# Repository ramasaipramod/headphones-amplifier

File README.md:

# Headphone Amplifier Using LM386

This project involves designing a headphone audio amplifier circuit using the LM386 low-voltage audio power amplifier. The amplifier boosts audio signals for use with headphones.

## Files in the Repository

- **`HeadphoneAmplifierUsingLM386.asc`**  
  LTspice simulation file to analyze the circuit's performance.
  
- **`HeadphoneAmplifierUsingLM386.brd`**  
  PCB layout file for the amplifier, which can be used to manufacture the circuit board.
  
- **`HeadphoneAmplifierUsingLM386.sch`**  
  Schematic diagram of the circuit showing all components and connections.

## Components Used
- LM386
- Resistors, capacitors, and other passive components.
- Headphone jack and connectors.

## How to Use
1. Open the **`.sch`** file in a schematic editor to view the circuit design.
2. Run the **`.asc`** file in LTspice to simulate and verify the circuit behavior.
3. Use the **`.brd`** file to fabricate the PCB, assemble the components, and test the amplifier.

## Tools Used
- **LTspice**: For circuit simulation.
- **EAGLE/Altium/Other PCB Design Software**: For schematic and PCB design.

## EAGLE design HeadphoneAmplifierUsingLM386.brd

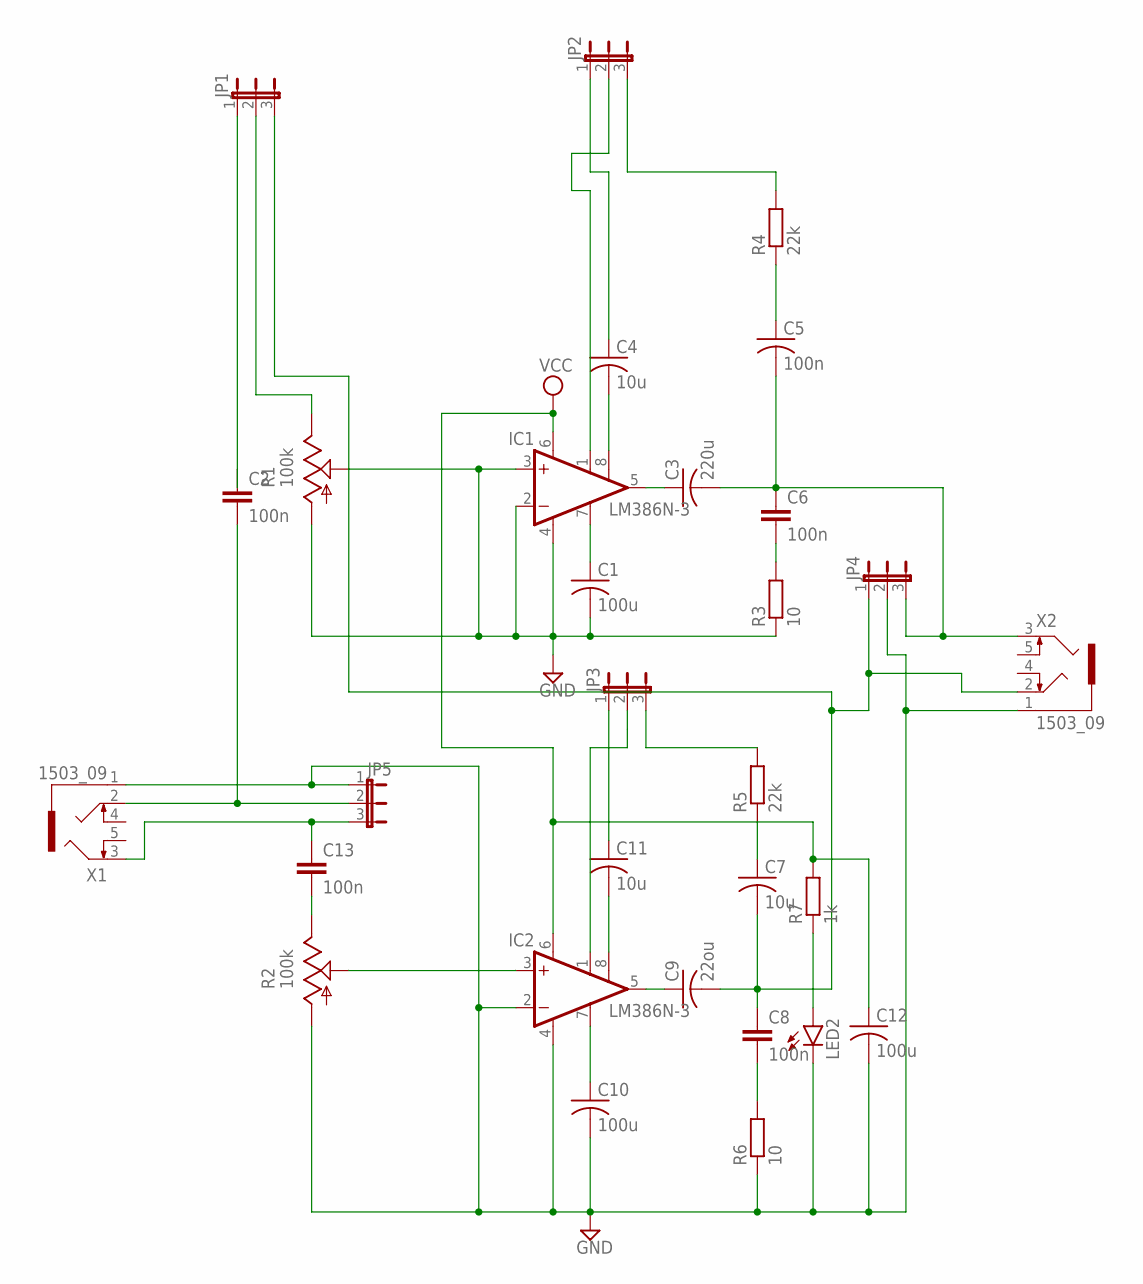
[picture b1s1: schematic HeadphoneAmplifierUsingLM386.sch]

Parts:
C1, C10, C12: 100u; C025-030X050
C2, C5, C6, C8, C13: 100n; C025-030X050
C3: 220u; C025-030X050
C4, C7, C11: 10u; C025-030X050
C9: 22ou; C025-030X050
IC1, IC2: LM386N-3; DIL08
JP1, JP2, JP3, JP4, JP5: JP2E; JP2
LED2: LED3MM
R1, R2: 100k; 3223W
R3, R6: 10; 0309/12
R4, R5: 22k; 0309/12
R7: 1k; 0309/12
X1, X2: 1503_09

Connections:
GND: C1.2, C10.2, C12.2, IC1.2 (-IN), IC1.3 (+IN), IC1.4 (GND), IC2.2 (-IN), IC2.4 (GND), JP4.2, JP5.1, LED2.K (C), R1.1 (A), R1.2 (S), R2.1 (A), R3.1, R6.1, X1.1, X2.1
unnamed: C2.1, JP1.1
unnamed: C4.2, IC1.8 (GAIN)
unnamed: IC2.3 (+IN), R2.2 (S)
unnamed: C1.1, IC1.7 (BYPASS)
unnamed: C3.1, IC1.5 (OUT)
unnamed: C3.2, C5.2, C6.1, JP4.3, X2.3
unnamed: C2.2, JP5.2, X1.2
unnamed: IC1.1 (GAIN), JP2.2
unnamed: C6.2, R3.2
unnamed: C7.2, C8.1, C9.2, JP1.3, JP4.1, X2.2
unnamed: C5.1, R4.1
unnamed: C7.1, R5.1
unnamed: JP2.3, R4.2
unnamed: C8.2, R6.2
unnamed: C10.1, IC2.7 (BYPASS)
unnamed: JP3.3, R5.2
unnamed: C9.1, IC2.5 (OUT)
unnamed: C11.2, IC2.8 (GAIN)
unnamed: IC2.1 (GAIN), JP3.2
unnamed: C11.1, JP3.1
unnamed: LED2.A, R7.1
unnamed: JP1.2, R1.3 (E)
unnamed: C13.2, R2.3 (E)
unnamed: C13.1, JP5.3, X1.3
unnamed: C4.1, JP2.1
VCC: C12.1, IC1.6 (VS), IC2.6 (VS), R7.2

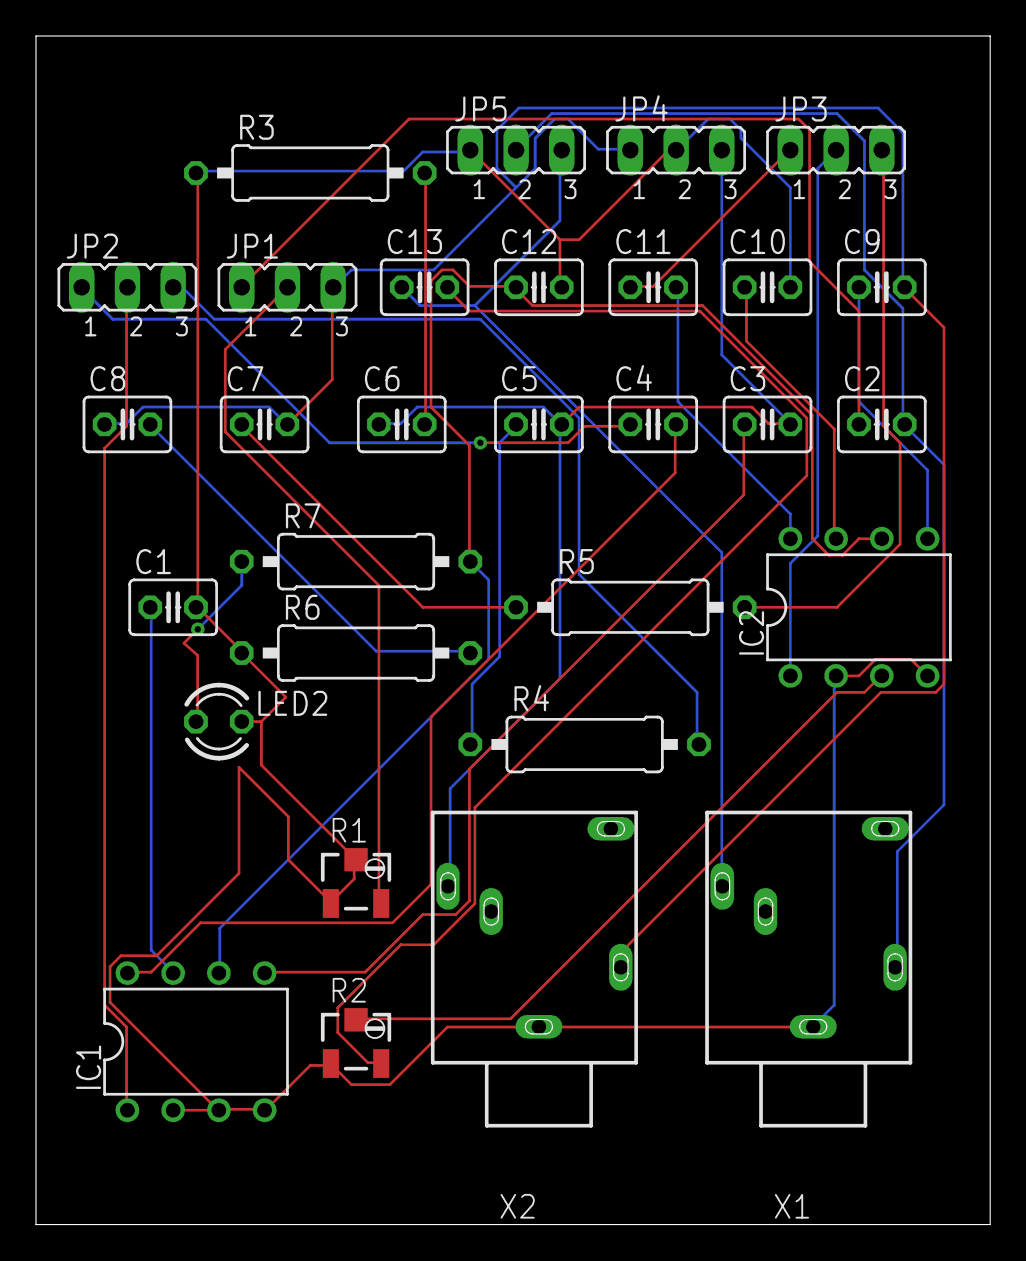
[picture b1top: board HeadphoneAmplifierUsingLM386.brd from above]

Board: 2 copper layers, 53.0 x 66.0 mm, 30 parts (0 on the bottom side), 27 nets.

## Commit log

2024-12-23 Initial commit with all files
